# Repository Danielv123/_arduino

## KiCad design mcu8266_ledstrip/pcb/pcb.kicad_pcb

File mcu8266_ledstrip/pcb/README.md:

These parts are downloaded from https://www.snapeda.com/parts/NodeMCU%20v2/Seeed%20Technology%20Co.,%20Ltd/view-part

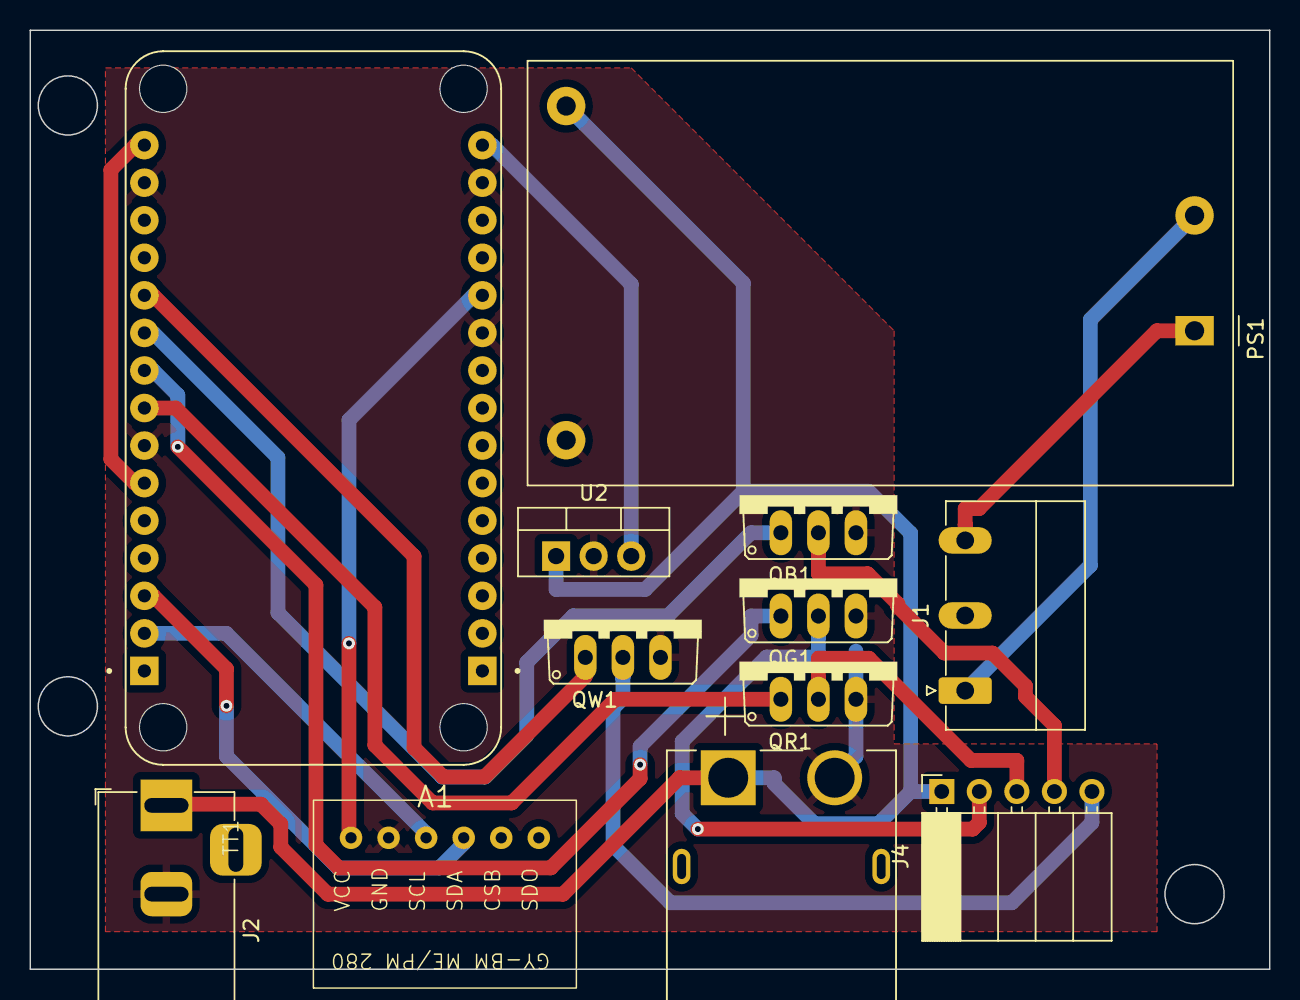
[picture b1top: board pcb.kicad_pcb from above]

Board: 2 copper layers, 83.8 x 63.5 mm, 12 parts (0 on the bottom side), 16 nets.

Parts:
A1: 113990105; SEEED_113990105
J1: Conn_01x03_Socket; PhoenixContact_MC_1,5_3-G-5.08_1x03_P5.08mm_Horizontal
J2: Screw_Terminal_01x02; BarrelJack_Horizontal
J4: Conn_01x05_Socket; PinSocket_1x05_P2.54mm_Horizontal
J5: XT60PW-M; AMASS_XT60PW-M
PS1: HLK-10M12; Converter_ACDC_HiLink_HLK-10Mxx
QB1: FQP30N06L; TO220V
QG1: FQP30N06L; TO220V
QR1: FQP30N06L; TO220V
QW1: FQP30N06L; TO220V
TT1: BME280
U2: LM7805_TO220; TO-220-3_Vertical

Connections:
GND: A1.J1_10 (GND), A1.J1_14 (GND), A1.J2_7 (GND), A1.J2_14 (GND), J2.2, J5.2 (-), PS1.3 (-Vout), QB1.3, QG1.3, QR1.3, QW1.3, TT1.2 (GND), U2.2 (GND)
unnamed: A1.J1_11 (3V3), TT1.1 (VCC)
unnamed: A1.J1_15 (VIN), U2.3 (VO)
unnamed: A1.J2_2 (D1), TT1.3 (SCL)
unnamed: A1.J2_3 (D2), TT1.4 (SDA)
unnamed: A1.J2_8 (D5), QR1.1
unnamed: A1.J2_9 (D6), QG1.1
unnamed: A1.J2_10 (D7), QB1.1
unnamed: A1.J2_11 (D8), QW1.1
unnamed: J1.1, PS1.2 (AC/N)
unnamed: J1.3, PS1.1 (AC/L)
unnamed: J2.1, J4.1, J5.1 (+), PS1.4 (+Vout), U2.1 (VI)
unnamed: J4.2, QG1.2
unnamed: J4.3, QR1.2
unnamed: J4.4, QB1.2
unnamed: J4.5, QW1.2

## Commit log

2019-02-13 Added current projects
2019-02-13 Updated dockerfile for power meter
2019-02-13 Added npm dependencies
2019-02-13 Avoided git clone in docker build for power_meter
2019-02-13 Use local pushgateway
2019-02-13 power_meter dockerfile
2023-09-17 Add ledstrip program and basic schematic
2023-09-24 Add kicad board
